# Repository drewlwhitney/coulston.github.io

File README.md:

Through my years of academic service as an Electrical and Computer Engineering professor
I've created a host of materials.  I am hoping that you might find these resources
helpful as a faculty or student.  Please 

# Contribute
An important feature of these notes is the ability for others to contribute to its ongoing improvement.
There are countless ways that you can improve this content.  If you are interested in contributing, reach out
to [Dr. Christopher Coulston](mailto:coulston@mines.edu?subject=[GitHub]%20Contributions) and I can arrange 
to make a branch of this repository.  I'd enjoy working with others and sharing perspectives.

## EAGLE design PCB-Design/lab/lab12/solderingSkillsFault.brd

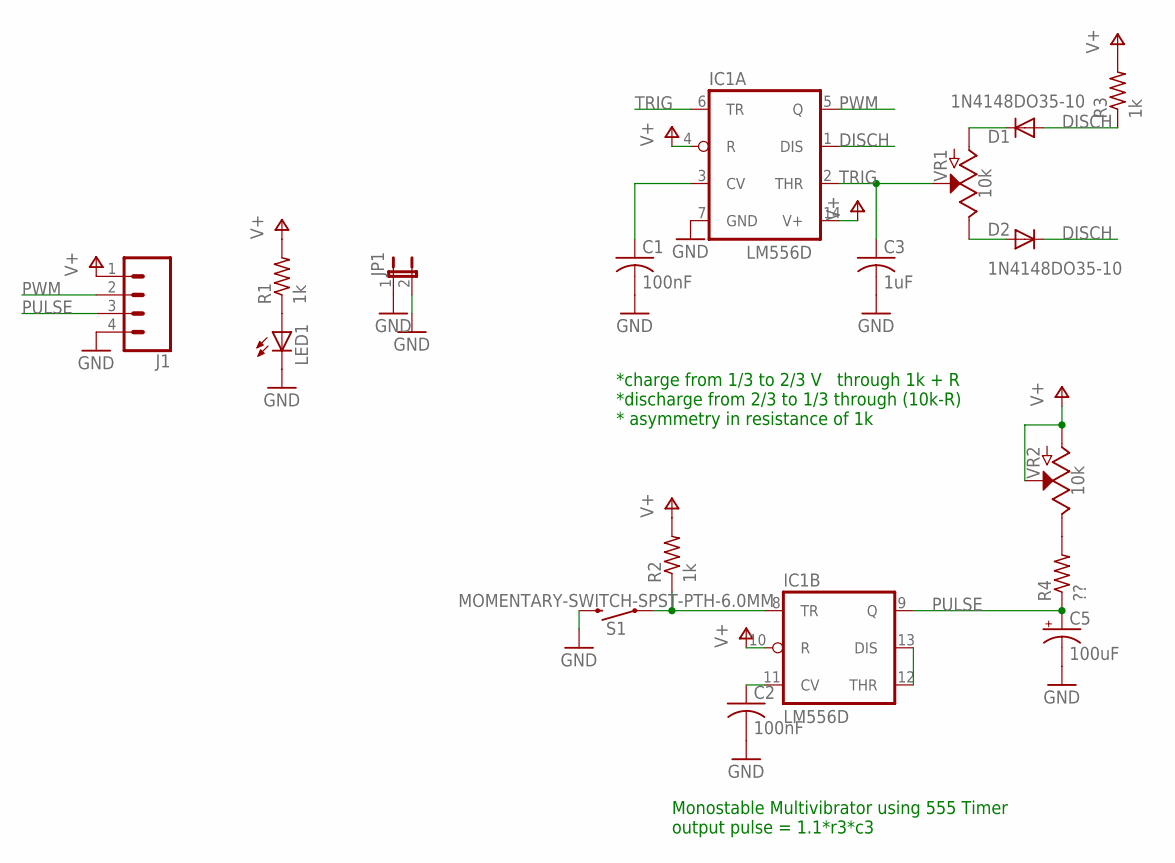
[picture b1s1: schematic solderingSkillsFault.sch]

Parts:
C1, C2: 100nF; C1206
C3: 1uF; C1206
C5: 100uF; PANASONIC_C
D1, D2: 1N4148DO35-10; DO35-10
IC1: LM556D; SO14
J1: CONN_04LOCK_LONGPADS; 1X04_LOCK_LONGPADS
JP1: JUMPER-2PTH_LOCK; 1X02_LOCK
LED1: LEDCHIPLED_1206; CHIPLED_1206
R1, R2, R3: 1k; M1206
R4: ??; M1206
S1: MOMENTARY-SWITCH-SPST-PTH-6.0MM; TACTILE_SWITCH_PTH_6.0MM
VR1, VR2: 10k; POT-PTH-ALPS

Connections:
DISCH: D1.A, D2.C, IC1.1 (DIS), R3.1
GND: C1.2, C2.2, C3.2, C5.-, IC1.7 (GND), J1.4, JP1.1, JP1.2, LED1.C, S1.3 (2)
unnamed: C1.1, IC1.3 (CV)
unnamed: D1.C, VR1.P$3 (A)
unnamed: D2.A, VR1.P$1 (E)
unnamed: IC1.8 (TR), R2.1, S1.1
unnamed: C2.1, IC1.11 (CV)
unnamed: LED1.A, R1.1
unnamed: IC1.12 (THR), IC1.13 (DIS)
unnamed: R4.2, VR2.P$1 (E)
PULSE: C5.+, IC1.9 (Q), J1.3, R4.1
PWM: IC1.5 (Q), J1.2
TRIG: C3.1, IC1.2 (THR), IC1.6 (TR), VR1.P$2 (S)
V+: IC1.4 (R), IC1.10 (R), IC1.14 (V+), J1.1, R1.2, R2.2, R3.2, VR2.P$2 (S), VR2.P$3 (A)

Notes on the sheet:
*charge from 1/3 to 2/3 V through 1k + R *discharge from 2/3 to 1/3 through (10k-R) * asymmetry in resistance of 1k
Monostable Multivibrator using 555 Timer output pulse = 1.1*r3*c3

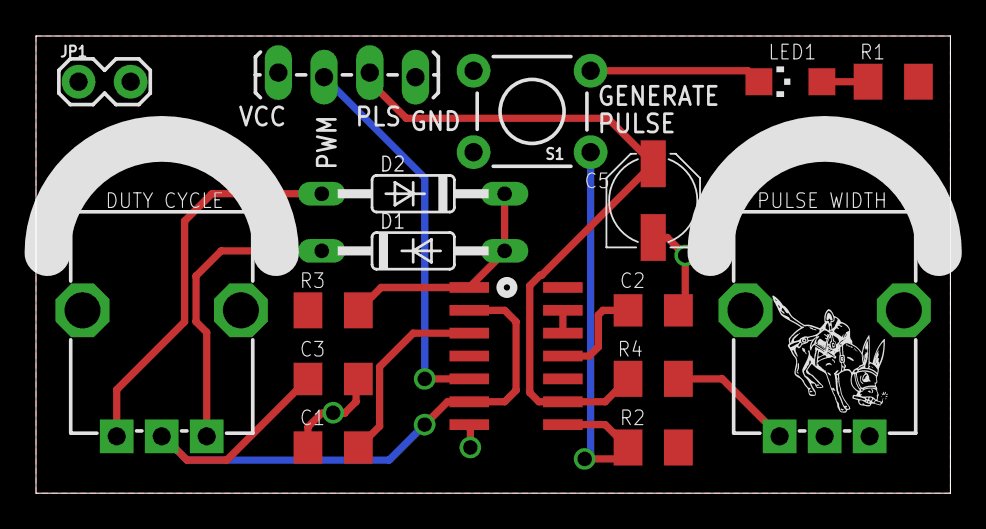
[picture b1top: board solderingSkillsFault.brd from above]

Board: 2 copper layers, 50.8 x 25.4 mm, 17 parts (0 on the bottom side), 14 nets.

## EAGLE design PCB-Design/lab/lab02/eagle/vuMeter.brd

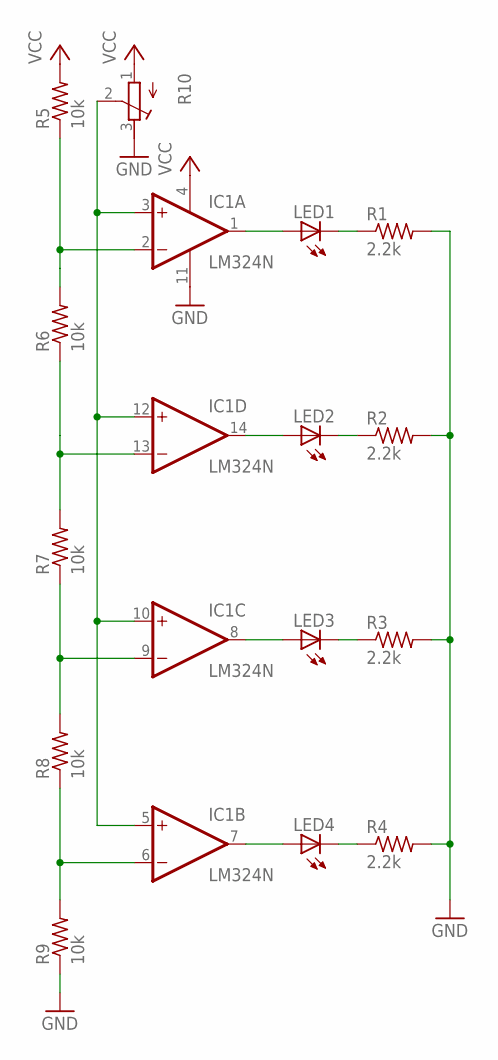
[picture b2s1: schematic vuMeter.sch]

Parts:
IC1: LM324N; DIL14
LED1, LED2, LED3, LED4: LED5MM
R1, R2, R3, R4: 2.2k; 0207/10
R5, R6, R7, R8, R9: 10k; 0207/10
R10: R-TRIMM3296W; RTRIM3296W

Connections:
GND: IC1.11 (V-), R1.2, R2.2, R3.2, R4.2, R9.1, R10.3 (E)
unnamed: IC1.2 (-IN), R5.1, R6.2
unnamed: IC1.13 (-IN), R6.1, R7.2
unnamed: IC1.9 (-IN), R7.1, R8.2
unnamed: IC1.6 (-IN), R8.1, R9.2
unnamed: IC1.1 (OUT), LED1.A
unnamed: LED1.K (C), R1.1
unnamed: IC1.14 (OUT), LED2.A
unnamed: LED2.K (C), R2.1
unnamed: IC1.8 (OUT), LED3.A
unnamed: IC1.7 (OUT), LED4.A
unnamed: LED4.K (C), R4.1
unnamed: LED3.K (C), R3.1
VCC: IC1.4 (V+), R5.2, R10.1 (A)
VIN: IC1.3 (+IN), IC1.5 (+IN), IC1.10 (+IN), IC1.12 (+IN), R10.2 (S)

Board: 2 copper layers, 15 parts (0 on the bottom side), 15 nets, no tracks yet.

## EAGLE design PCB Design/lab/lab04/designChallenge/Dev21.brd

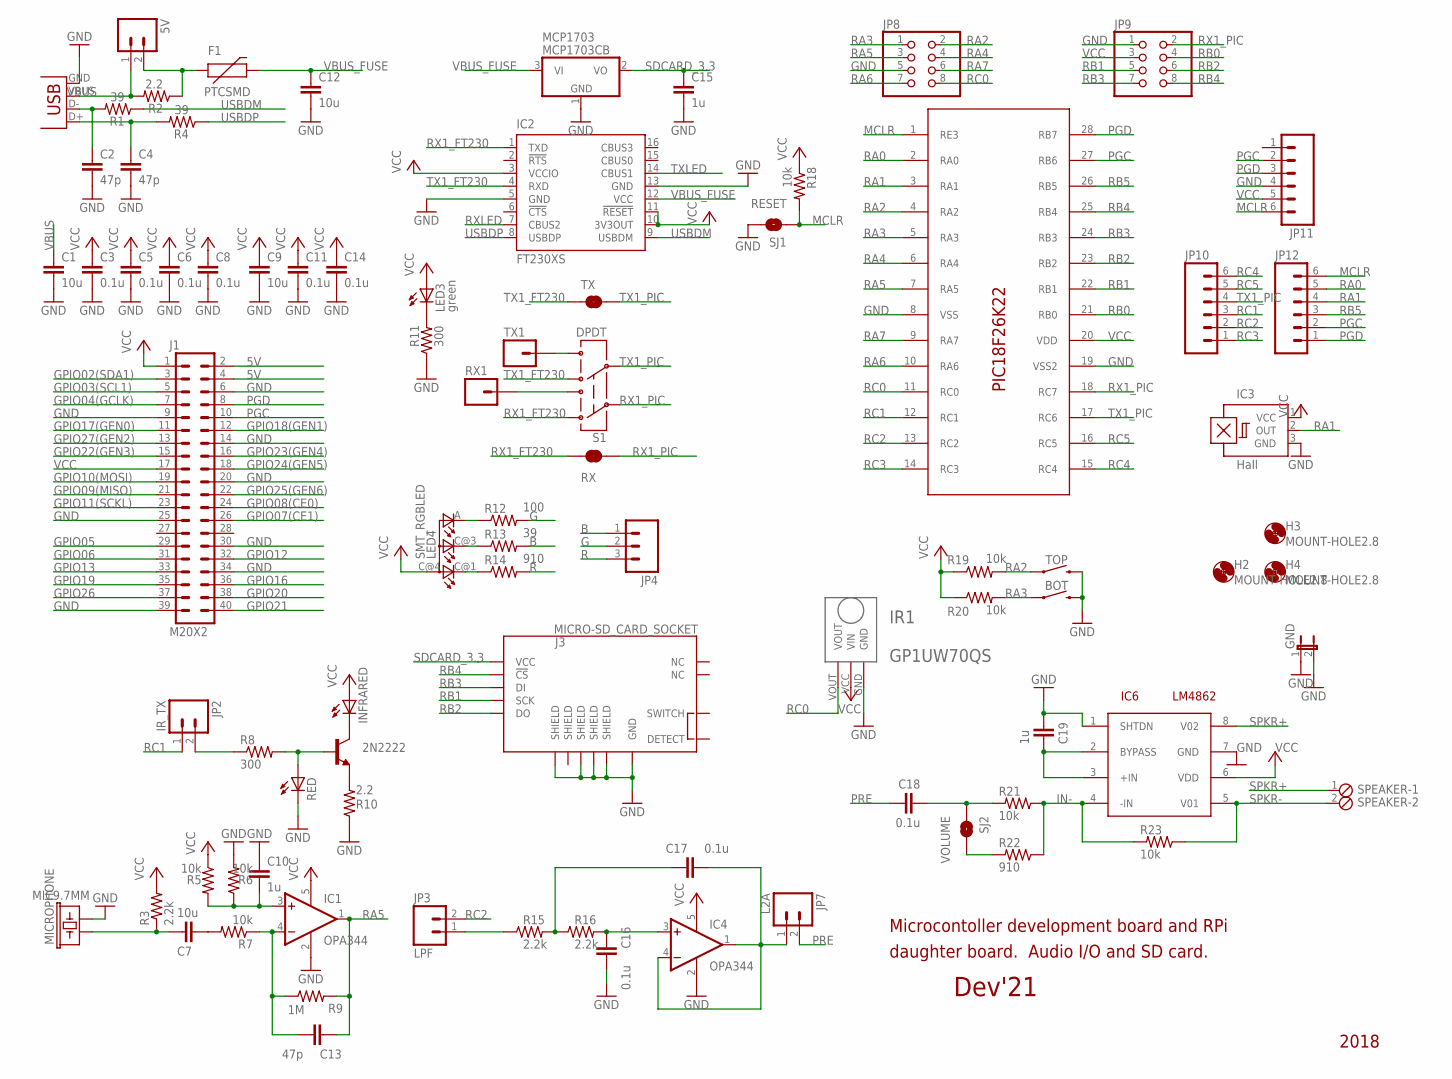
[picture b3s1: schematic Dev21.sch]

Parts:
2N2222: TRANSISTOR_NPNSOT23-3; SOT23-3
5V: M02LOCK; 1X02_LOCK
BOT: MOMENTARY-SWITCH-SPST-SMD-5.2MM; TACTILE_SWITCH_SMD_5.2MM
C1, C7, C9, C12: 10u; C1206
C2, C4, C13: 47p; C1206
C3, C5, C6, C8, C11, C14, C16, C17, C18: 0.1u; C1206
C10, C15, C19: 1u; C1206
F1: PTCSMD; PTC-1206
GND: JP1E; JP1
H2, H3, H4: MOUNT-HOLE2.8; 2,8
IC1, IC4: OPA344; SOT23-5
IC2: FT230XS; SSOP16
IC3: Hall; SOT23-W
IC6: LM4862; SO08
INFRARED: LED1206; LED-1206
IR1: GP1UW70QS
J1: M20X2; 2X20
J3: MICRO-SD_CARD_SOCKET; MICRO-SD-SOCKET
JP2: IR_TX; 1X02_LOCK
JP3: LPF; 1X02_LOCK
JP4: M03LOCK; 1X03_LOCK
JP7: L2A; 1X02_LOCK
JP8, JP9: PINHD-2X4; 2X04
JP10, JP11, JP12: M06LOCK; 1X06_LOCK
LED3: green; LED-1206
LED4: SMT_RGBLED; P-LCC-4
MCP1703: MCP1703CB; SOT23
MICROPHONE: MIC9.7MM; MIC-9.7MM
PIC18F26K22: PIC18F26J2228SSOP; SSOP28DB
R1, R4, R13: 39; R1206
R2, R10: 2.2; R1206
R3, R15, R16: 2.2k; R1206
R5, R6, R7, R18, R19, R20, R21, R23: 10k; R1206
R8, R11: 300; R1206
R9: 1M; R1206
R12: 100; R1206
R14, R22: 910; R1206
RED: LED1206; LED-1206
RX: SJ_NC; SMT-JUMPER_2_NC_TRACE_NO-SILK
RX1: M01PTH; 1X01
S1: DPDT; AYZ0202
SJ1: RESET; SJ_2S-NOTRACE
SJ2: VOLUME; SJ_2S-NOTRACE
SPEAKER: MPT2; 2POL254
TOP: MOMENTARY-SWITCH-SPST-SMD-5.2MM; TACTILE_SWITCH_SMD_5.2MM
TX: SJ_NC; SMT-JUMPER_2_NC_TRACE_NO-SILK
TX1: M01PTH; 1X01
X1: USBSMD; USB-MINIB

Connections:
5V: J1.2, J1.4
B: JP4.1, R13.2
G: JP4.2, R12.2
GND: BOT.3 (2), C1.2, C2.2, C3.2, C4.2, C5.2, C6.2, C8.2, C9.2, C10.1, C11.2, C12.2, C14.2, C15.2, C16.1, C19.2, GND.1, GND.2, IC1.2 (V-), IC2.5 (GND), IC2.13 (GND), IC3.3 (GND), IC4.2 (V-), IC6.1 (SHTDN), IC6.7 (GND), IR1.GND, J1.6, J1.9, J1.14, J1.20, J1.25, J1.30, J1.34, J1.39, J3.GND, J3.SHIELD1 (SHIELD), J3.SHIELD3 (SHIELD), J3.SHIELD4 (SHIELD), J3.SHIELD5 (SHIELD), JP8.5, JP9.1, JP11.4, MCP1703.1 (GND), MICROPHONE.2, PIC18F26K22.8 (VSS), PIC18F26K22.19 (VSS2), R6.2, R10.1, R11.1, RED.C, SJ1.2, TOP.3 (2), X1.GND
GPIO02(SDA1): J1.3
GPIO03(SCL1): J1.5
GPIO04(GCLK): J1.7
GPIO05: J1.29
GPIO06: J1.31
GPIO07(CE1): J1.26
GPIO08(CE0): J1.24
GPIO09(MISO): J1.21
GPIO10(MOSI): J1.19
GPIO11(SCKL): J1.23
GPIO12: J1.32
GPIO13: J1.33
GPIO16: J1.36
GPIO17(GEN0): J1.11
GPIO18(GEN1): J1.12
GPIO19: J1.35
GPIO20: J1.38
GPIO21: J1.40
GPIO22(GEN3): J1.15
GPIO23(GEN4): J1.16
GPIO24(GEN5): J1.18
GPIO25(GEN6): J1.22
GPIO26: J1.37
GPIO27(GEN2): J1.13
IN-: IC6.4 (-IN), R21.1, R22.1, R23.2
MCLR: JP11.6, JP12.6, PIC18F26K22.1 (RE3), R18.2, SJ1.1
MIC: C13.1, IC1.4 (-IN), R7.1, R9.1
unnamed: C16.2, IC4.3 (+IN), R16.2
unnamed: C17.2, R15.2, R16.1
unnamed: C17.1, IC4.1 (OUT), IC4.4 (-IN), JP7.1
unnamed: JP3.1, R15.1
unnamed: C2.1, R1.2, X1.D-
unnamed: C4.1, R4.2, X1.D+
unnamed: C7.1, MICROPHONE.1, R3.1
unnamed: C7.2, R7.2
unnamed: 5V.2, F1.1, R2.1
unnamed: C10.2, IC1.3 (+IN), R5.2, R6.1
unnamed: RX1.1, S1.3
unnamed: LED4.C@1 (CRED), R14.1
unnamed: LED4.A (CGREEN), R12.1
unnamed: 2N2222.3 (C), INFRARED.C
unnamed: LED3.C, R11.2
unnamed: 2N2222.2 (E), R10.2
unnamed: LED4.C@3 (CBLUE), R13.1
unnamed: 2N2222.1 (B), R8.2, RED.A
unnamed: C19.1, IC6.2 (BYPASS), IC6.3 (+IN)
unnamed: JP2.2, R8.1
unnamed: S1.6, TX1.1
unnamed: C18.1, R21.2, SJ2.1
unnamed: R22.2, SJ2.2
PGC: J1.10, JP11.2, JP12.2, PIC18F26K22.27 (RB6)
PGD: J1.8, JP11.3, JP12.1, PIC18F26K22.28 (RB7)
PRE: C18.2, JP7.2
R: JP4.3, R14.2
RA0: JP12.5, PIC18F26K22.2 (RA0)
RA1: IC3.2 (OUT), JP12.4, PIC18F26K22.3 (RA1)
RA2: JP8.2, PIC18F26K22.4 (RA2), R19.2, TOP.1
RA3: BOT.1, JP8.1, PIC18F26K22.5 (RA3), R20.2
RA4: JP8.4, PIC18F26K22.6 (RA4)
RA5: C13.2, IC1.1 (OUT), JP8.3, PIC18F26K22.7 (RA5), R9.2
RA6: JP8.7, PIC18F26K22.10 (RA6)
RA7: JP8.6, PIC18F26K22.9 (RA7)
RB0: JP9.4, PIC18F26K22.21 (RB0)
RB1: J3.SCLK (SCK), JP9.5, PIC18F26K22.22 (RB1)
RB2: J3.DO, JP9.6, PIC18F26K22.23 (RB2)
RB3: J3.DI, JP9.7, PIC18F26K22.24 (RB3)
RB4: J3.CS (!CS), JP9.8, PIC18F26K22.25 (RB4)
RB5: JP12.3, PIC18F26K22.26 (RB5)
RC0: IR1.VOUT, JP8.8, PIC18F26K22.11 (RC0)
RC1: JP2.1, JP10.3, PIC18F26K22.12 (RC1)
RC2: JP3.2, JP10.2, PIC18F26K22.13 (RC2)
RC3: JP10.1, PIC18F26K22.14 (RC3)
RC4: JP10.6, PIC18F26K22.15 (RC4)
RC5: JP10.5, PIC18F26K22.16 (RC5)
RX1_FT230: IC2.1 (TXD), RX.1, S1.1
RX1_PIC: JP9.2, PIC18F26K22.18 (RC7), RX.2, S1.2
RXLED: IC2.7 (CBUS2)
SDCARD_3.3: C15.1, J3.VCC, MCP1703.2 (VO)
SPKR+: IC6.8 (V02), SPEAKER.1
SPKR-: IC6.5 (V01), R23.1, SPEAKER.2
TX1_FT230: IC2.4 (RXD), S1.4, TX.1
TX1_PIC: JP10.4, PIC18F26K22.17 (RC6), S1.5, TX.2
TXLED: IC2.14 (CBUS1)
USBDM: IC2.9 (USBDM), R1.1
USBDP: IC2.8 (USBDP), R4.1
VBUS: 5V.1, C1.1, R2.2, X1.VBUS
VBUS_FUSE: C12.1, F1.2, IC2.12 (VCC), MCP1703.3 (VI)
VCC: C3.1, C5.1, C6.1, C8.1, C9.1, C11.1, C14.1, IC1.5 (V+), IC2.3 (VCCIO), IC2.10 (3V3OUT), IC2.11 (!RESET), IC3.1 (VCC), IC4.5 (V+), IC6.6 (VDD), INFRARED.A, IR1.VCC (VIN), J1.1, J1.17, JP9.3, JP11.5, LED3.A, LED4.C@4 (A), PIC18F26K22.20 (VDD), R3.2, R5.1, R18.1, R19.1, R20.1

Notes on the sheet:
Microcontoller development board and RPi
daughter board. Audio I/O and SD card.
2018
Dev'21

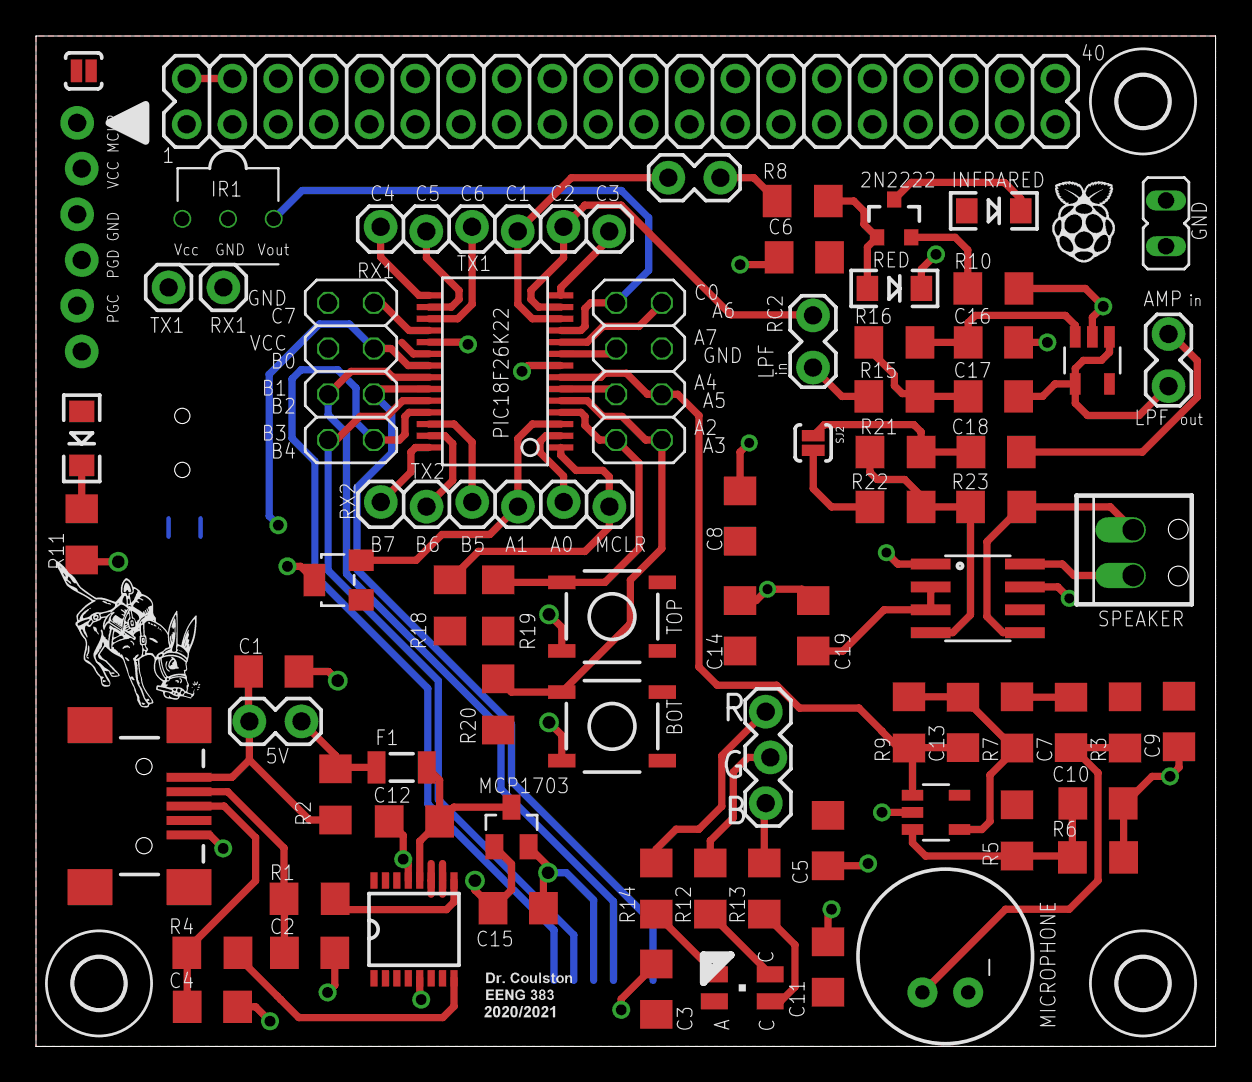
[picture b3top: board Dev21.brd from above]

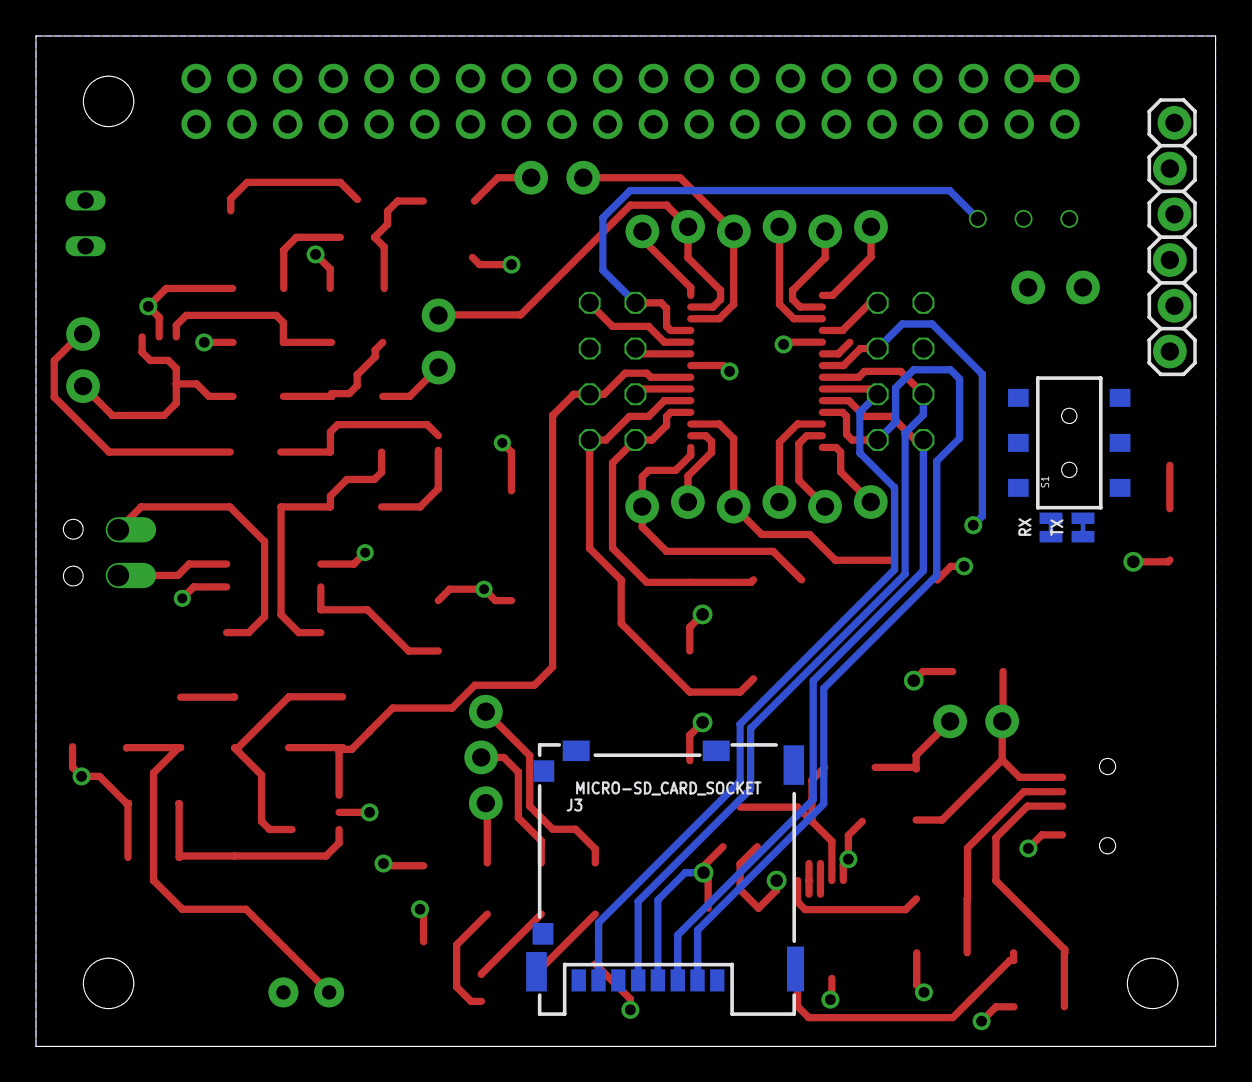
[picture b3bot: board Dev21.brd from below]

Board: 2 copper layers, 65.5 x 56.1 mm, 83 parts (5 on the bottom side), 66 nets.

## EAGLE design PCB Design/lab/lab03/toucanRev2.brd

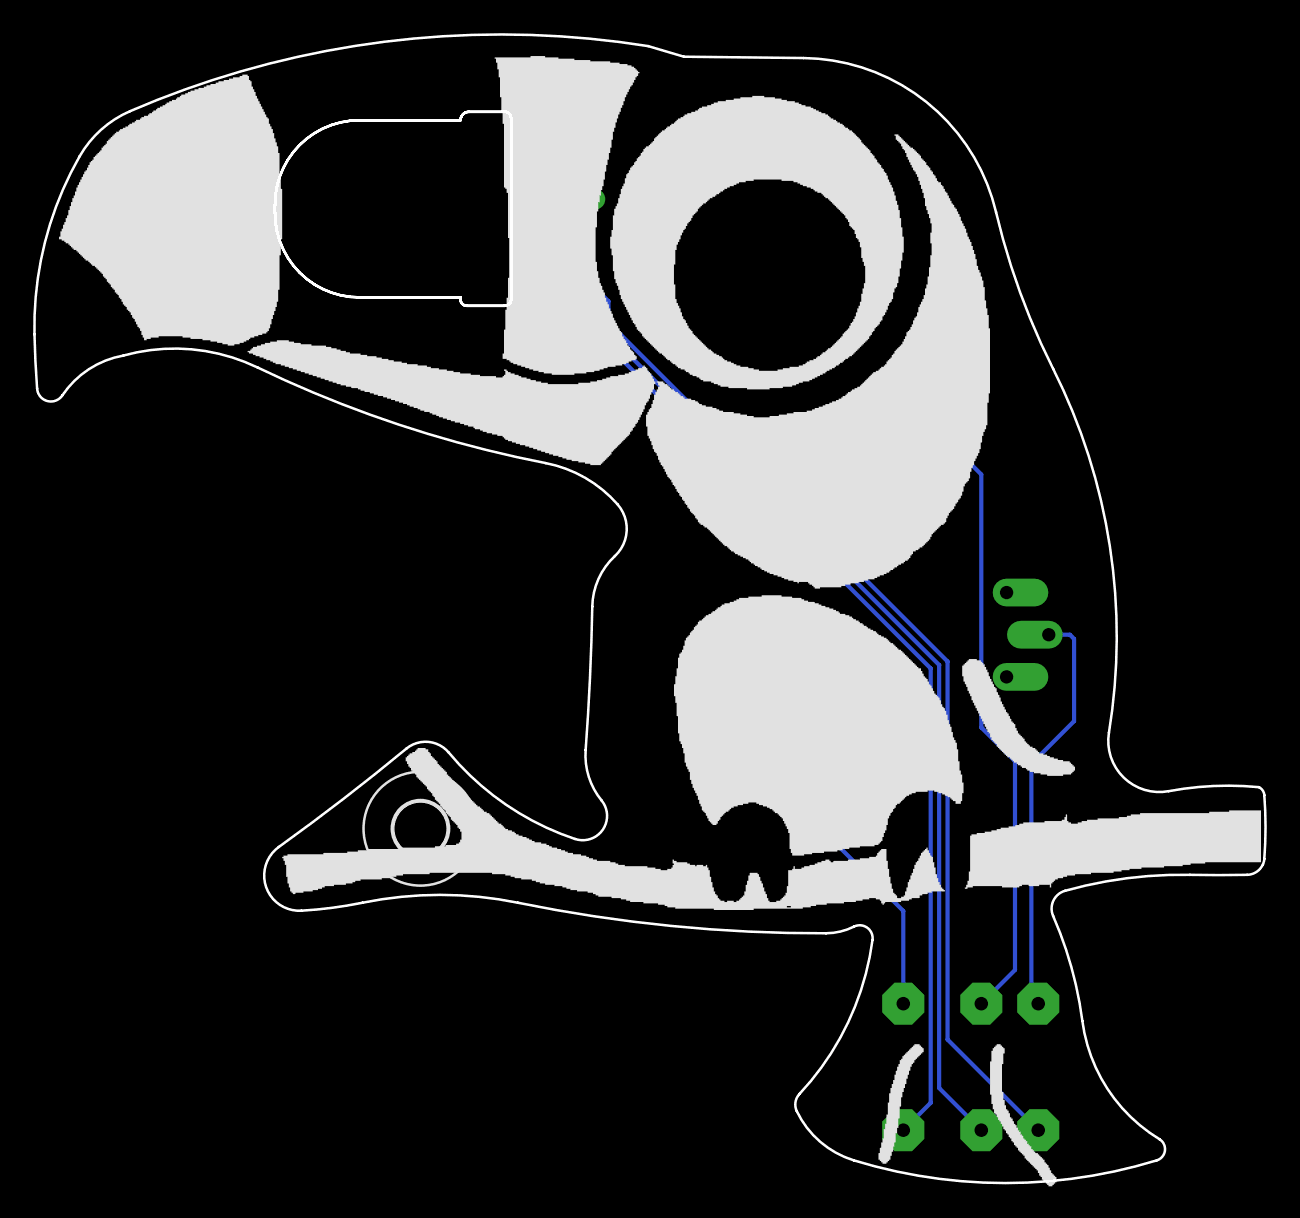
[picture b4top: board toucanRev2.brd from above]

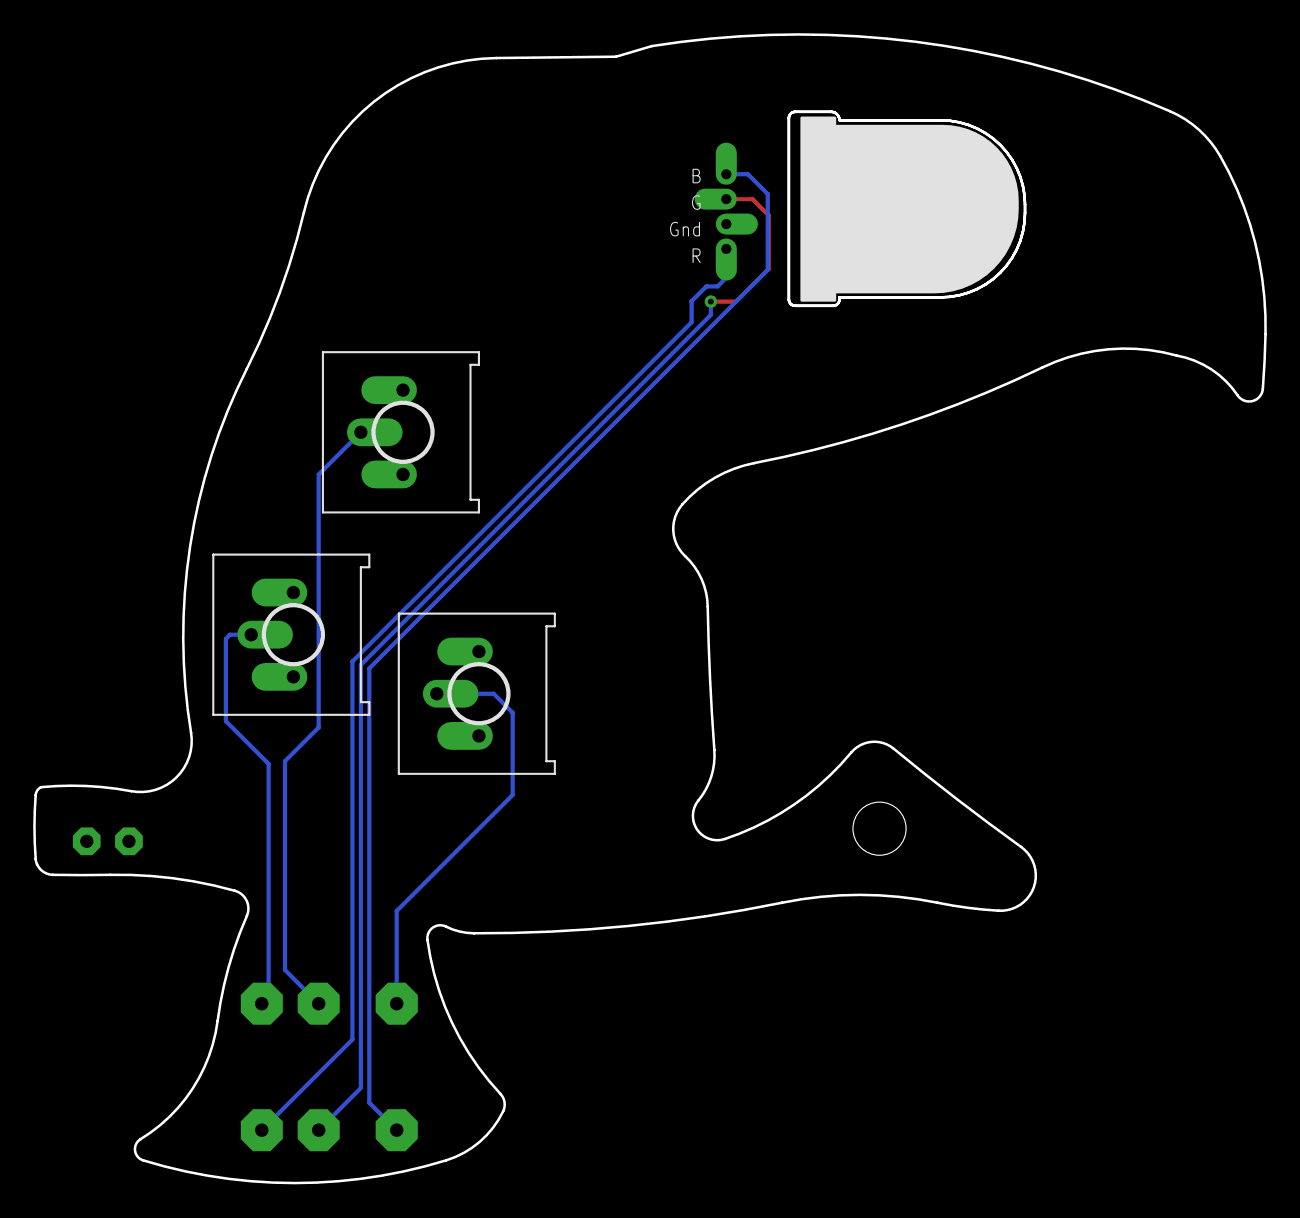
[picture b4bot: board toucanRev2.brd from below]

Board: 2 copper layers, 74.2 x 69.2 mm, 9 parts (7 on the bottom side), 8 nets.

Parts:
10MM: RGBLED-CARIGHT_ANGLE; RGB10MM_FLAT
BLUE: 1kΩ; 0207/12
GREEN: 1kΩ; 0207/12
H1: MOUNT-HOLE3.2; 3,2
PWR: 2POS_HEADERJUMPER; 2HEADER
RED: 1kΩ; 0207/12
U$2, U$4, U$5: 10kΩ; S63P

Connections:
BLUE_2_LED: 10MM.PIN4, BLUE.2
BLUE_2_POT: BLUE.1, U$4.CENTER
GND: PWR.P$2, U$2.LEFT, U$4.LEFT, U$5.LEFT
GREEN_2_LED: 10MM.PIN3, GREEN.2
GREEN_2_POT: GREEN.1, U$2.CENTER
RED_2_LED: 10MM.PIN1, RED.2
RED_2_POT: RED.1, U$5.CENTER
VCC: 10MM.PIN2, PWR.P$1

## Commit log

2025-04-14 Trying to run a web page on Git
    Frist push
2025-04-14 push bootstrap folder
    bootstrap makes the pages look nicer
2025-04-14 Uploading lab and lecture content
2025-04-14 Organizing Web Pages
2025-04-14 Create index.html
    Main launch page, checking how hyperlinks work
2025-04-14 Delete README.md
    I want web browsers to default to index.html It seems when there is a README.md file this becomes the default landing page on coulston.github.io
2025-04-14 Push additional materials
2025-04-22 Upload 393 and 484 web
    Big archive push to Git
2025-04-22 remove blank from folder title
2025-04-22 resolving dead links
    Adding the least amount of material to get the pages working correctly.
2025-05-07 Update index.html
    Added "ab" in front to get pull-down menu's to work. Nothing else has so let's give this a try!
2025-05-07 Update index.html
    Added links to bootstrap - get rid of local library
2025-05-07 Update index.html
    Update to comtemporary Bootstrap
2025-05-07 Update index.html
    Format changes
2025-05-07 Update index.html
    Convert to comtemporary BootStrap with URL reference to get rid of local library.
2025-05-07 Update index.html
    Added back Le javascript to auto advance the .carousel
2025-05-07 Update index.html
    Fix bad GitHub home link
2025-05-07 Deleted bootstrap folder
    Good riddance
2025-05-16 Adding to linuxInstall.html
    As I work through creating a linux development environment on my own, I'm adding to linuxInstall.html at the same time. Currently the instructions to running the installer are finished.
2025-05-16 Update pwm_tbWaveSetup.tcl
    Added some better and consistent comments to TCL header
2025-05-16 Update lab header
2025-05-16 Frontpage editing
2025-05-16 update index
2025-05-16 Another index.html template
2025-05-16 YAHP
    Yet another home page
2025-05-16 YAHP
2025-05-16 Converging on YAHP
2025-05-16 Added dropdown in Navbar - maybe?
2025-05-16 edits to main page
2025-05-18 Remade home page
    Not great, but functional
2025-05-20 Update linuxInstall.html
    Nearly final instructions for linux installation finished
2025-05-20 Quick rendering fixes to linuxInstall.html
2025-05-20 Update inlab02.html
    Standalone Project got renamed to Application Project(s) in new versions of MPLAB. Changing this, as it caused some confusion last semester.
2025-05-23 Add repository links
2025-05-29 Fixing formatting
2025-05-29 Fix formatting
2025-07-16 Update lecture04.html
    Clear up confusion between count and currentCount
2025-07-16 Fix count in lecture 04
    There was ambiguity between count and currentCount in the diagrams and VHDL code.
2025-07-16 Fix images for count
2025-07-16 Added PDF of intro digital text
2025-07-16 Delete .bak files
    When spell checking these files are generated by ispell
2025-07-16 upload syllabus to 484
2025-07-16 Update index.html
    syllabus link
2025-07-28 removed old lecture notes
2025-08-10 Update index.html
    Included date column
2025-08-10 Update index.html
    Fixed format and added date column
2025-08-11 Update index.html
    Fix formatting issues
2025-08-11 Update index.html
    Last set of syntax errors fixes :/
2025-08-11 Update index.html
    added HW5-7
2025-08-12 Deleted Homework folder
    Because this has been moved off the website to Gradescope and Canvas
2025-08-19 Update howTo 00 Install Xilinx Vitas.docx
    Added Kenny's observations about driver issues.
2025-09-02 updated linux install instructions
2025-09-02 fixed verison error
2025-09-08 Fixed EENG 484 Home Link
    Fixed home link from throwing 404. (removed /lab from intended home url)
2025-09-12 Add Ubuntu shortcut instructions
2025-09-15 Update content of inlab03 to melody
2025-09-15 inlab03 Touch-ups
2025-09-15 Update basicBuildingBlocksVhdl.zip
    Fixed fnc ='1' in generic adder subtractor
2025-09-16 Replace MCC Classic image with Melody
2025-09-17 add Melody lab3/4
2025-09-22 inlab04 prelim edits
2025-09-22 inlab04 finish MCC settings
2025-09-22 finalize inlab04.c and lab04.c
2025-09-22 remove todo (oops)
2025-09-22 Update classic/melody with existing files
2025-09-22 Update lab1Architecture.png
    Fixed ch1 input to scopeFace to ch1Wave. Ditto to ch2
2025-09-26 Update question to match answer guide
2025-09-29 Update lab05 webpage
2025-10-03 Add handouts for lectures 16 and 17
2025-10-03 Update index.html
    Made consistent handout (not plural) directory for all the lecture PDFs
2025-10-03 handout directory
    Changed the name of the handout directory to be consistent with the links in the lecture notes.
2025-10-05 (in)Lab06 and small other fixes
2025-10-05 quick edits
2025-10-05 (in)Lab07 updates
2025-10-05 Fix bullet points inlab07
2025-10-06 Still trying to fix inlab07
2025-10-06 Fixed stopwatch dp figure
    Needed to run the counter into the mux and register
2025-10-06 Update stopWatchDp&Cu.pdf
    Updated the associated handout with the stopwatch datapath
2025-10-09 Updated the inLab05 document, Q20, to more clearly state what the last row wants
2025-10-10 Fixed the label for the IR decoder in Q12 to match with the schematic
2025-10-10 Updated Q15 on inLab6 to tell students to attach a screenshot (per the answer key)
2025-10-12 Converting inlab08. No changes needed for lab08
2025-10-12 Fixed the table on above Q22 to say "Ch2" instead of "Ch1" twice
2025-10-15 upload a handout and tech docs
2025-10-16 Fix error in inlab07
2025-10-24 Add lines students need to delete from MCC Melody code to get correct timer period
2025-10-26 Update inlab09
2025-10-26 fix intro inlab09.c
2025-10-26 fix table inlab09
2025-10-26 Replace inlab09.c and sdCard files
2025-10-28 Update the signal acquire architecture
    The converted values will be from the analog range 3.3V to 0V. The image and lab text now agree to split this range into 5 equal parts.
2025-10-28 Update signalAcquire_architecture.bmp
    Fixed the missing "000" on the over sampling output from the signalAcquire module
2025-10-29 Create simpleDualPortRam.pdf
    Needed this handout
2025-10-29 Add TMR0 code patch directions and explanantion page
2025-10-29 Correct webpage title
2025-10-30 Fixed the inLab9 document to use MCC Melody function names instead of MCC classic ones. Updated the inLab09.c file to use the MCC Melody functions instead of MCC Classic functions
2025-10-30 Removed the part after Q10 about modifying the TMR0H and TMR0L registers, since these appear to be read-only in MCC Melody
2025-10-31 Clarify where students should find PIC RAM size
2025-11-02 Update acquireToHdmi lectures and images
    Cleaned up the images associated with this lab to make them more understandable. Updated the associated PDF handout to have the correct class name :/
2025-11-03 Update inlab10
    Pending .c files and lab10. Check-in for website rendering
2025-11-03 Update lab10 and .c files
2025-11-03 Misc fixes
2025-11-03 still fixing inlab10...
2025-11-03 Give up on fixing bullet points - my IDE doesn't match <ul> with </ul>
2025-11-05 Fix broken block ram link
2025-11-09 lab11 conversion
2025-11-12 update enhanced PWM lecture/lab
2025-11-13 Vitis 2022 to 2024
    Changing from Vitis 2022 to 2024. Big improvement on spooky errors.
2025-11-14 update footers in files
    Changed 498 to 484
2025-11-14 Update Vitis instructions
2025-11-15 Update howTo 08 Build IP For Zynq.docx
    Modifications to 2024
2025-11-15 Update to 2024
    There were some needed updates to make the howTo current.
2025-11-17 update naming for 2024
    The wrapper names have changes when migrating from 2022 to 2024.
2025-11-23 Fixed a dead link in the inLab14 document. It now correctly points to the Honcell battery datasheet
2025-11-23 Clarified that the sweep duration is the duration of the *entire* sweep, not the time to hold at each increment. Also specified that the sweep should be repeated until the user presses a key to stop 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
2026-02-13 Adjusted Q14 to include the line number in the question. Students were getting confused about this
2026-02-13 Fixed the instructions before Q6 to refer to UART1 instead of EUSART1

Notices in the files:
parts and their libraries:
SparkFun-Connectors: Licensing: Creative Commons ShareAlike 4.0 International - https://creativecommons.org/licenses/by-sa/4.0
